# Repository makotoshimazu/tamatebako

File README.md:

TAMATEBAKO Project
====

まとんの結婚式で出すための玉手箱

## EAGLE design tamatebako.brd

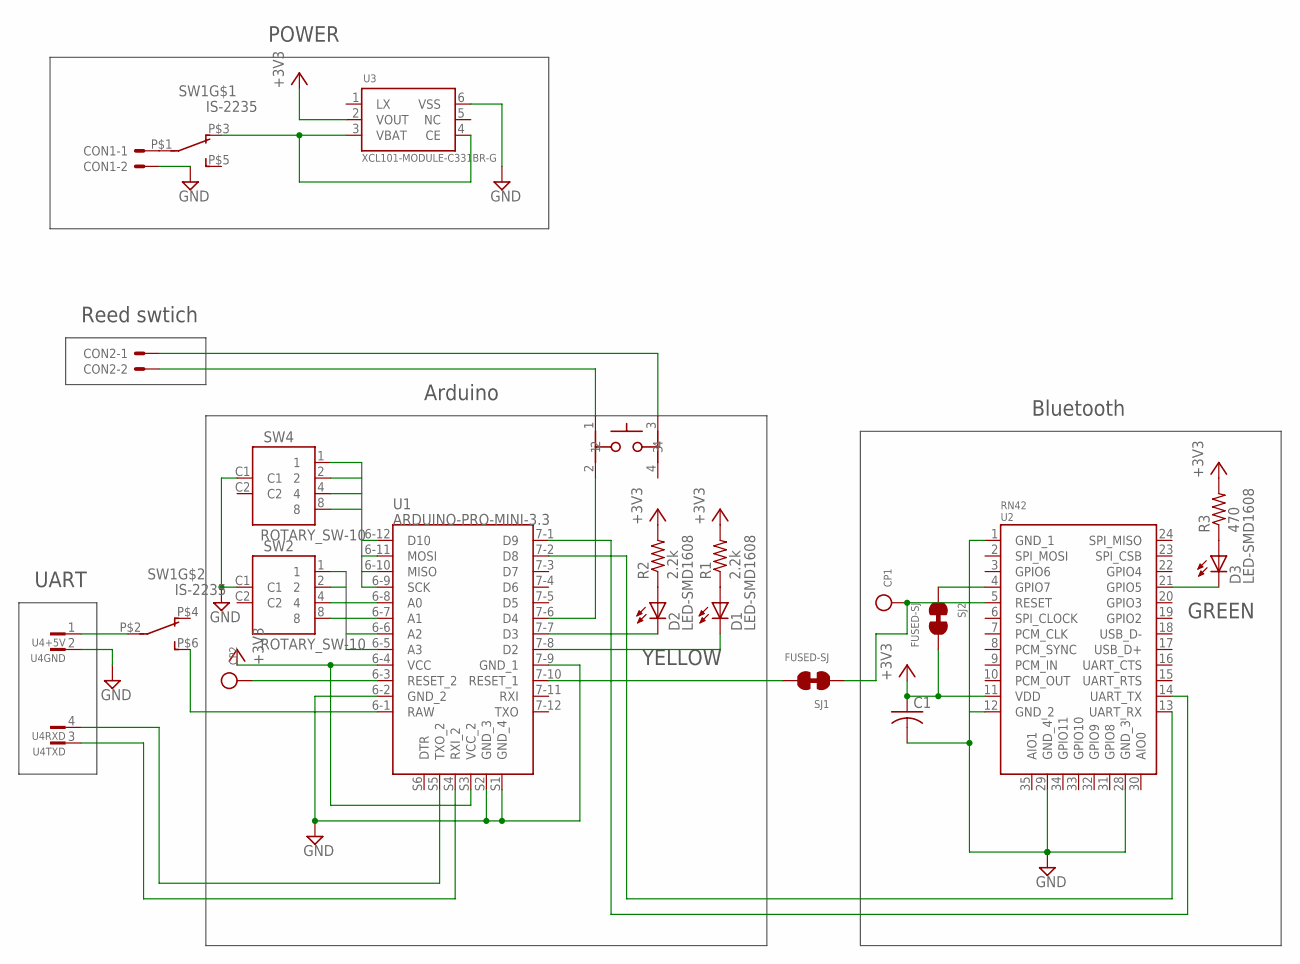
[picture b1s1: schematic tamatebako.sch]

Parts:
C1: C-2012; 2012-C
CON1, CON2: PH_CONNECTOR_2PIN
CP1, CP2: SST-1-2
D1, D2, D3: LED-SMD1608; D1608
R1, R2: 2.2k; 2012-R
R3: 470; 2012-R
SJ1, SJ2: FUSED-SJ
SW1: IS-2235
SW2, SW4: ROTARY_SW-10; ROTARY_SW
SW3: PUSHSW
U1: ARDUINO-PRO-MINI-3.3; ARDUINO_PRO_MINI
U2: RN42
U3: XCL101-MODULE-C331BR-G; XCL101-MODULE
U4: UART_MODULE; MICRO_USB_SERIAL_MODULE

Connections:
+3V3: C1.1, R1.2, R2.2, R3.2, SJ2.2, U1.6-4 (VCC), U1.S3 (VCC_2), U2.11 (VDD), U3.2 (VOUT)
GND: C1.2, CON1.2, SW2.C1, SW4.C1, U1.6-2 (GND_2), U1.7-9 (GND_1), U1.S1 (GND_4), U1.S2 (GND_3), U2.1 (GND_1), U2.12 (GND_2), U2.28 (GND_3), U2.29 (GND_4), U3.6 (VSS), U4.2
LOWER0: SW2.1, U1.6-8 (A0)
LOWER1: SW2.2, U1.6-7 (A1)
LOWER2: SW2.4, U1.6-6 (A2)
LOWER3: SW2.8, U1.6-5 (A3)
unnamed: CON1.1, SW1.P$1
unnamed: SW1.P$3 (O), U3.3 (VBAT), U3.4 (CE)
unnamed: CP1.1, SJ1.1, U2.5 (RESET)
unnamed: U1.S5 (TXO_2), U4.4
unnamed: U1.7-1 (D9), U2.14 (UART_TX)
unnamed: D1.A, R1.1
unnamed: D2.A, R2.1
unnamed: U1.S4 (RXI_2), U4.3
unnamed: SW1.P$2, U4.1
unnamed: SW1.P$6 (S), U1.6-1 (RAW)
unnamed: D2.K, U1.7-7 (D3)
unnamed: D1.K, U1.7-8 (D2)
unnamed: SW3.2, U1.7-6 (D4)
unnamed: CON2.2, SW3.1
unnamed: CON2.1, SW3.3
unnamed: SJ2.1, U2.4 (GPIO7)
unnamed: D3.A, R3.1
unnamed: D3.K, U2.21 (GPIO5)
unnamed: U1.7-2 (D8), U2.13 (UART_RX)
RESET_ARDUINO: SJ1.2, U1.7-10 (RESET_1)
RESET_ARDUINO_2: CP2.1, U1.6-3 (RESET_2)
UPPER0: SW4.1, U1.6-12 (D10)
UPPER1: SW4.2, U1.6-11 (MOSI)
UPPER2: SW4.4, U1.6-10 (MISO)
UPPER3: SW4.8, U1.6-9 (SCK)

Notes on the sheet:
Reed swtich
POWER
UART
GREEN
YELLOW
Bluetooth
Arduino

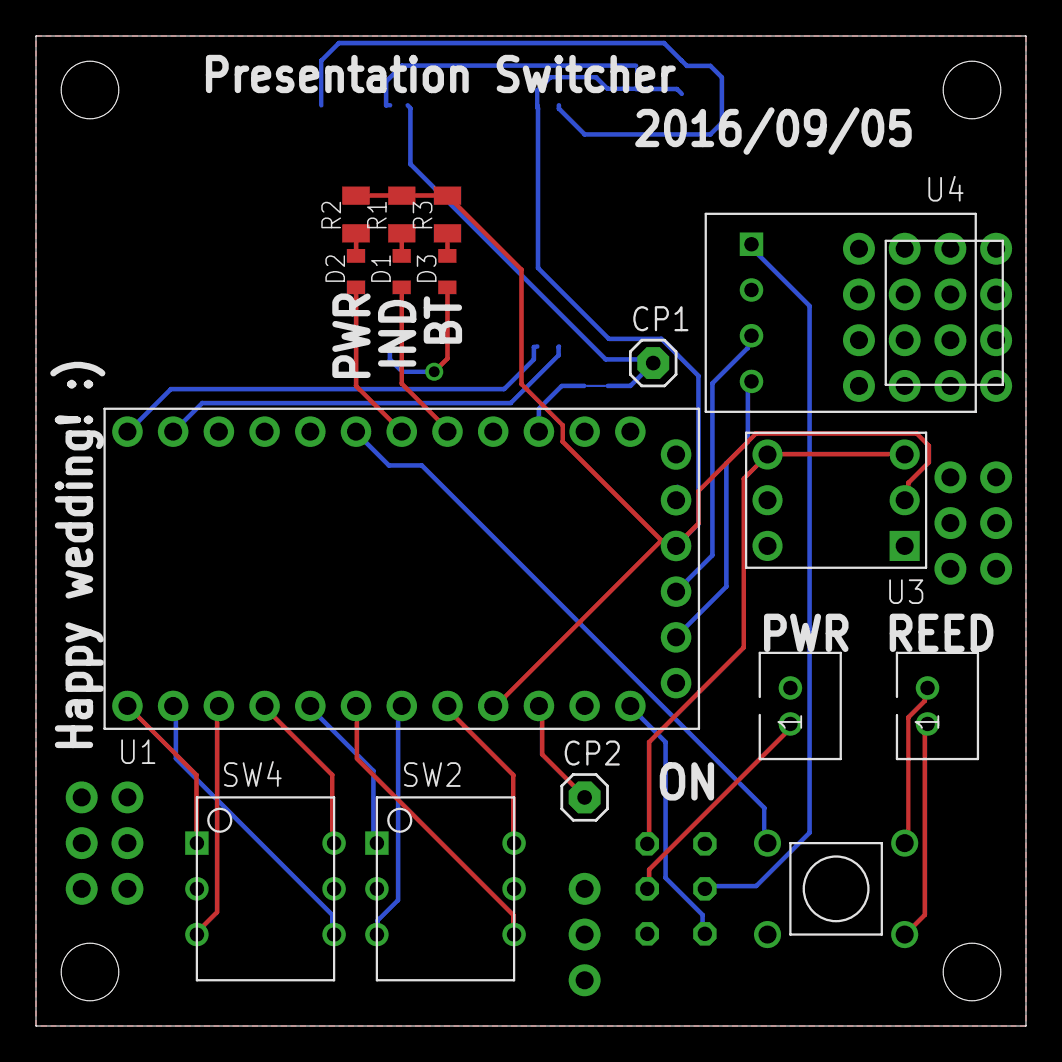
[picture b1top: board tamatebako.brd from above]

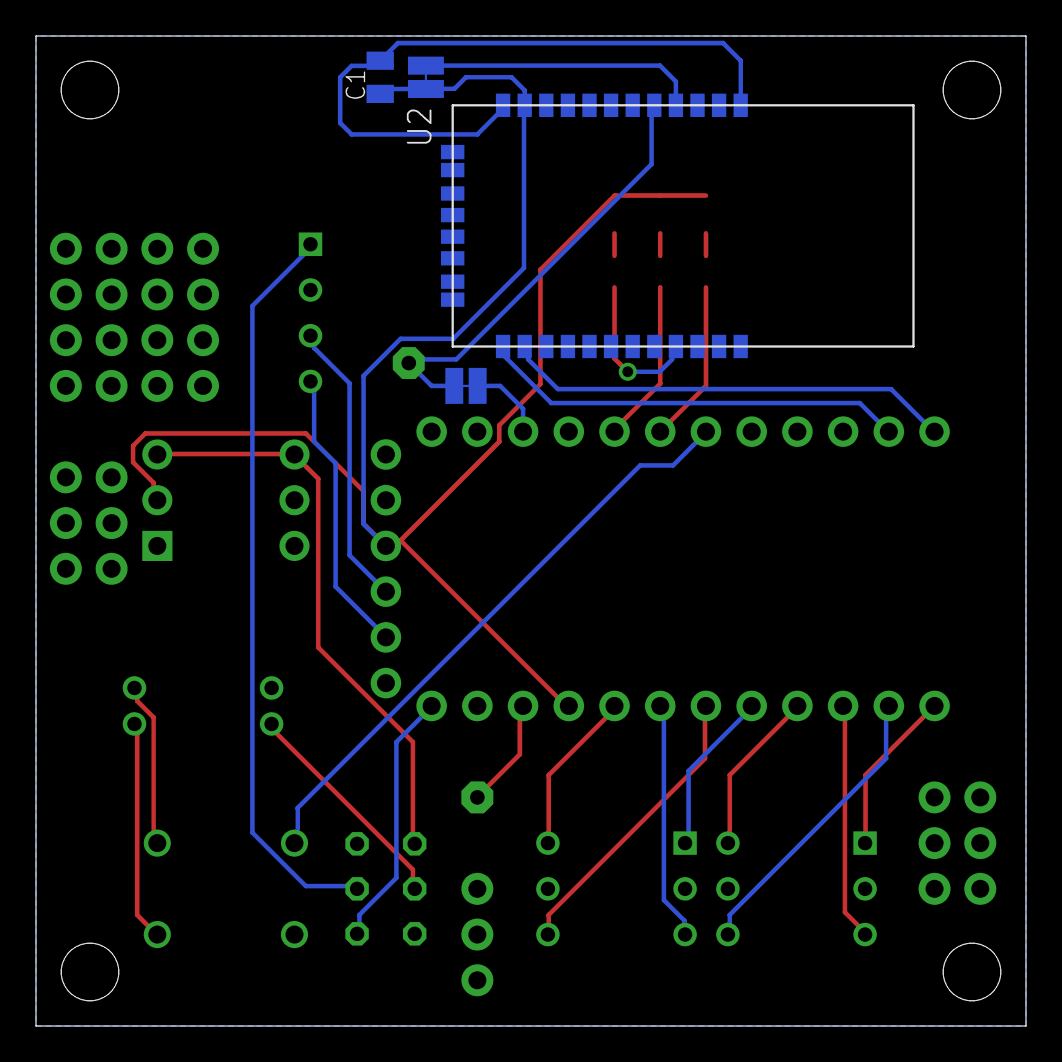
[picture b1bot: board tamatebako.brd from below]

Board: 2 copper layers, 55.0 x 55.0 mm, 21 parts (4 on the bottom side), 31 nets.

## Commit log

2016-09-04 回路図書いた
2016-09-04 ロータリースイッチの追加とボード図の作成
2018-02-17 Final
